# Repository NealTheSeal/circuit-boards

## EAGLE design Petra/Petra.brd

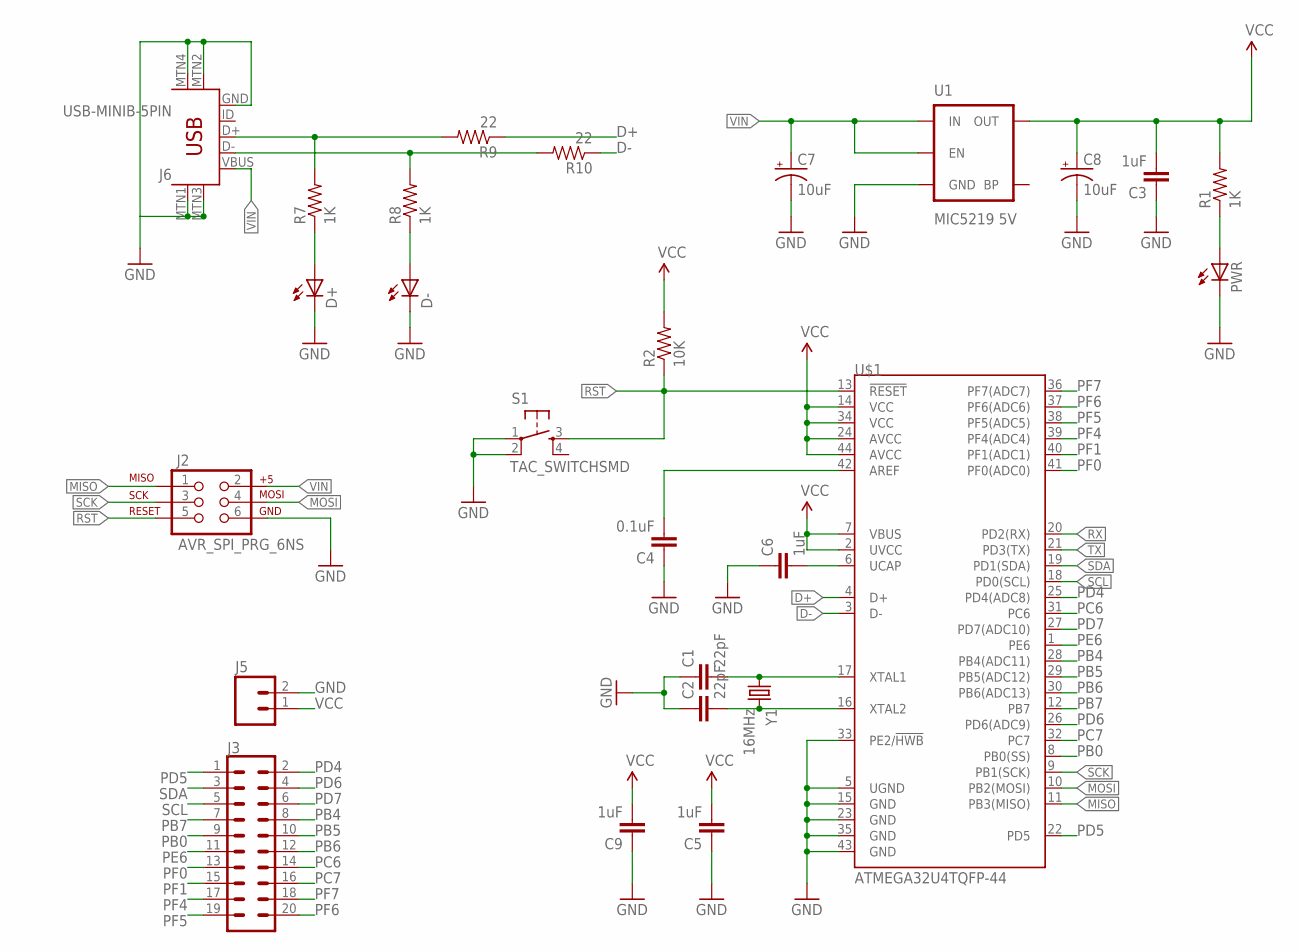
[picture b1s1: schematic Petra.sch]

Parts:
C1, C2: 22pF; 0402-CAP
C3, C5, C6, C9: 1uF; 0402-CAP
C4: 0.1uF; 0402-CAP
C7, C8: 10uF; EIA3216
D+: LEDCHIP-LED0805; CHIP-LED0805
D-: LEDCHIP-LED0805; CHIP-LED0805
J2: AVR_SPI_PRG_6NS; 2X3-NS
J3: CONN_10X2; 2X10
J5: M02PTH; 1X02
J6: USB-MINIB-5PIN; USB-MINIB
PWR: LEDCHIP-LED0805; CHIP-LED0805
R1, R7, R8: 1K; 0603-RES
R2: 10K; 0603-RES
R9, R10: 22; 0603-RES
S1: TAC_SWITCHSMD; TAC-SWITCH-PTH
U1: MIC5219 5V; SOT23-5
U$1: ATMEGA32U4TQFP-44; TQFP44
Y1: 16MHz; CRYSTAL-SMD-5X3

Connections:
D+: R9.1, U$1.4 (D+)
D-: R10.1, U$1.3 (D-)
GND: C1.1, C2.1, C3.1, C4.1, C5.1, C6.1, C7.C (-), C8.C (-), C9.1, D+.C, D-.C, J2.6, J5.2, J6.GND, J6.MTN1 (MTN2), J6.MTN2 (MTN3), J6.MTN3 (MTN1), J6.MTN4, PWR.C, S1.1, S1.2, U1.2 (GND), U$1.5 (UGND), U$1.15 (GND), U$1.23 (GND), U$1.33 (PE2/!HWB), U$1.35 (GND), U$1.43 (GND)
MISO: J2.1, U$1.11 (PB3(MISO))
MOSI: J2.4, U$1.10 (PB2(MOSI))
unnamed: C1.2, U$1.17 (XTAL1), Y1.1
unnamed: C2.2, U$1.16 (XTAL2), Y1.3 (2)
unnamed: C6.2, U$1.6 (UCAP)
unnamed: C4.2, U$1.42 (AREF)
unnamed: PWR.A, R1.1
unnamed: D-.A, R8.1
unnamed: D+.A, R7.1
unnamed: J6.D+, R7.2, R9.2
unnamed: J6.D-, R8.2, R10.2
PB0: J3.9, U$1.8 (PB0(SS))
PB4: J3.8, U$1.28 (PB4(ADC11))
PB5: J3.10, U$1.29 (PB5(ADC12))
PB6: J3.12, U$1.30 (PB6(ADC13))
PB7: J3.7, U$1.12 (PB7)
PC6: J3.14, U$1.31 (PC6)
PC7: J3.16, U$1.32 (PC7)
PD4: J3.2, U$1.25 (PD4(ADC8))
PD5: J3.1, U$1.22 (PD5)
PD6: J3.4, U$1.26 (PD6(ADC9))
PD7: J3.6, U$1.27 (PD7(ADC10))
PE6: J3.11, U$1.1 (PE6)
PF0: J3.13, U$1.41 (PF0(ADC0))
PF1: J3.15, U$1.40 (PF1(ADC1))
PF4: J3.17, U$1.39 (PF4(ADC4))
PF5: J3.19, U$1.38 (PF5(ADC5))
PF6: J3.20, U$1.37 (PF6(ADC6))
PF7: J3.18, U$1.36 (PF7(ADC7))
RST: J2.5, R2.1, S1.3, U$1.13 (!RESET)
RX: U$1.20 (PD2(RX))
SCK: J2.3, U$1.9 (PB1(SCK))
SCL: J3.5, U$1.18 (PD0(SCL))
SDA: J3.3, U$1.19 (PD1(SDA))
TX: U$1.21 (PD3(TX))
VCC: C3.2, C5.2, C8.A (+), C9.2, J5.1, R1.2, R2.2, U1.5 (OUT), U$1.2 (UVCC), U$1.7 (VBUS), U$1.14 (VCC), U$1.24 (AVCC), U$1.34 (VCC), U$1.44 (AVCC)
VIN: C7.A (+), J2.2, J6.VBUS, U1.1 (IN), U1.3 (EN)

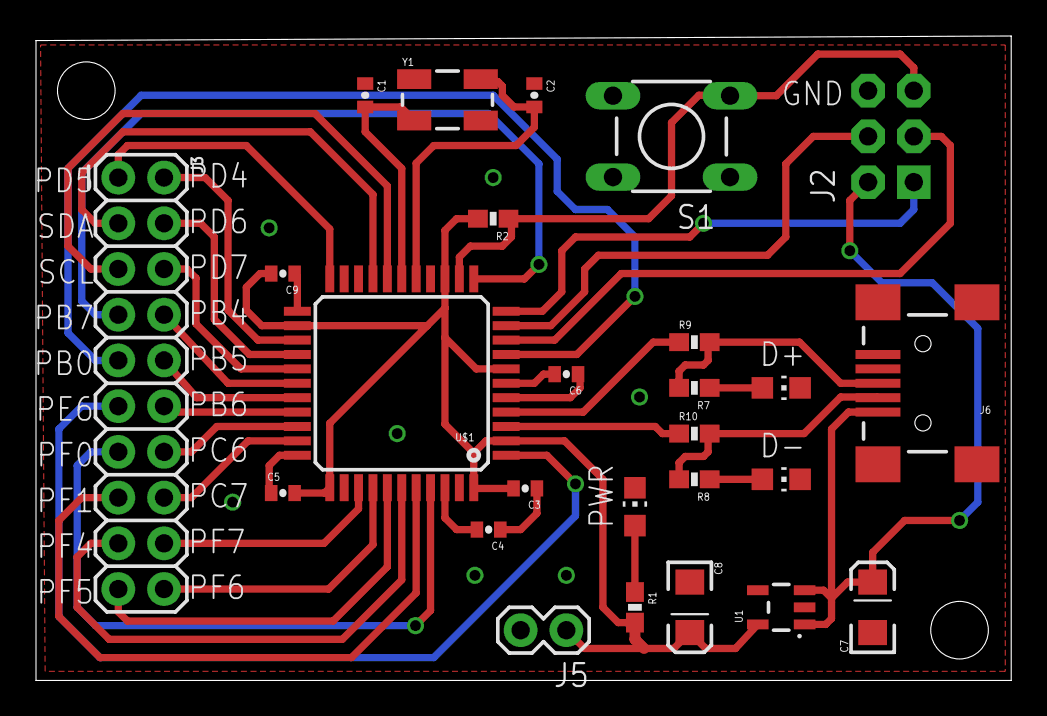
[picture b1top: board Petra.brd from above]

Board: 2 copper layers, 54.2 x 35.8 mm, 26 parts (0 on the bottom side), 38 nets.

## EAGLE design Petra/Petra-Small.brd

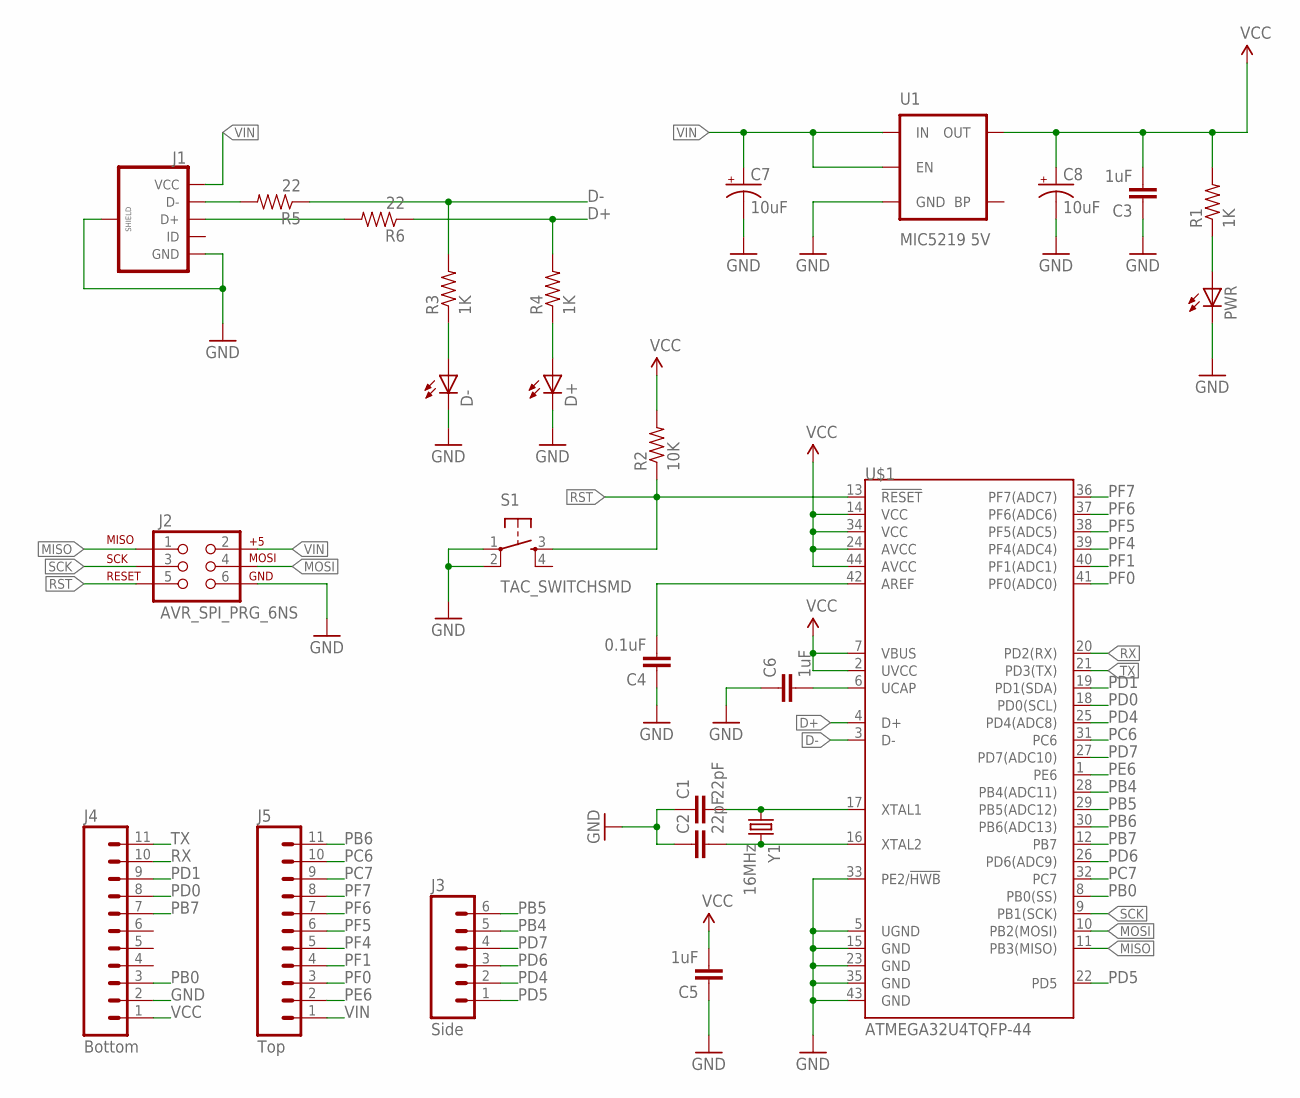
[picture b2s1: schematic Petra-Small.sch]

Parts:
C1, C2: 22pF; 0402-CAP
C3, C5, C6: 1uF; 0402-CAP
C4: 0.1uF; 0402-CAP
C7, C8: 10uF; EIA3216
D+: LEDCHIP-LED0805; CHIP-LED0805
D-: LEDCHIP-LED0805; CHIP-LED0805
J1: USB_MICROB_PLUGCONN-11752; USB-B-MICRO-SMD_V03
J2: AVR_SPI_PRG_6NS; 2X3-NS
J3: Side; 1X06
J4: Bottom; 1X11
J5: Top; 1X11
PWR: LEDCHIP-LED0805; CHIP-LED0805
R1, R3, R4: 1K; 0603-RES
R2: 10K; 0603-RES
R5, R6: 22; 0603-RES
S1: TAC_SWITCHSMD; TACTILE-SWITCH-SMD
U1: MIC5219 5V; SOT23-5
U$1: ATMEGA32U4TQFP-44; TQFP44
Y1: 16MHz; CRYSTAL-SMD-5X3

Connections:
D+: R4.2, R6.1, U$1.4 (D+)
D-: R3.2, R5.1, U$1.3 (D-)
GND: C1.1, C2.1, C3.1, C4.1, C5.1, C6.1, C7.C (-), C8.C (-), D+.C, D-.C, J1.GND, J1.SHIELD1 (SHIELD), J1.SHIELD2 (SHIELD), J1.SHIELD3 (SHIELD), J2.6, J4.2, PWR.C, S1.1, S1.2, U1.2 (GND), U$1.5 (UGND), U$1.15 (GND), U$1.23 (GND), U$1.33 (PE2/!HWB), U$1.35 (GND), U$1.43 (GND)
MISO: J2.1, U$1.11 (PB3(MISO))
MOSI: J2.4, U$1.10 (PB2(MOSI))
unnamed: C1.2, U$1.17 (XTAL1), Y1.1
unnamed: C2.2, U$1.16 (XTAL2), Y1.3 (2)
unnamed: C6.2, U$1.6 (UCAP)
unnamed: C4.2, U$1.42 (AREF)
unnamed: J1.D-, R5.2
unnamed: J1.D+, R6.2
unnamed: PWR.A, R1.1
unnamed: D+.A, R4.1
unnamed: D-.A, R3.1
PB0: J4.3, U$1.8 (PB0(SS))
PB4: J3.5, U$1.28 (PB4(ADC11))
PB5: J3.6, U$1.29 (PB5(ADC12))
PB6: J5.11, U$1.30 (PB6(ADC13))
PB7: J4.7, U$1.12 (PB7)
PC6: J5.10, U$1.31 (PC6)
PC7: J5.9, U$1.32 (PC7)
PD0: J4.8, U$1.18 (PD0(SCL))
PD1: J4.9, U$1.19 (PD1(SDA))
PD4: J3.2, U$1.25 (PD4(ADC8))
PD5: J3.1, U$1.22 (PD5)
PD6: J3.3, U$1.26 (PD6(ADC9))
PD7: J3.4, U$1.27 (PD7(ADC10))
PE6: J5.2, U$1.1 (PE6)
PF0: J5.3, U$1.41 (PF0(ADC0))
PF1: J5.4, U$1.40 (PF1(ADC1))
PF4: J5.5, U$1.39 (PF4(ADC4))
PF5: J5.6, U$1.38 (PF5(ADC5))
PF6: J5.7, U$1.37 (PF6(ADC6))
PF7: J5.8, U$1.36 (PF7(ADC7))
RST: J2.5, R2.1, S1.3, U$1.13 (!RESET)
RX: J4.10, U$1.20 (PD2(RX))
SCK: J2.3, U$1.9 (PB1(SCK))
TX: J4.11, U$1.21 (PD3(TX))
VCC: C3.2, C5.2, C8.A (+), J4.1, R1.2, R2.2, U1.5 (OUT), U$1.2 (UVCC), U$1.7 (VBUS), U$1.14 (VCC), U$1.24 (AVCC), U$1.34 (VCC), U$1.44 (AVCC)
VIN: C7.A (+), J1.VBUS (VCC), J2.2, J5.1, U1.1 (IN), U1.3 (EN)

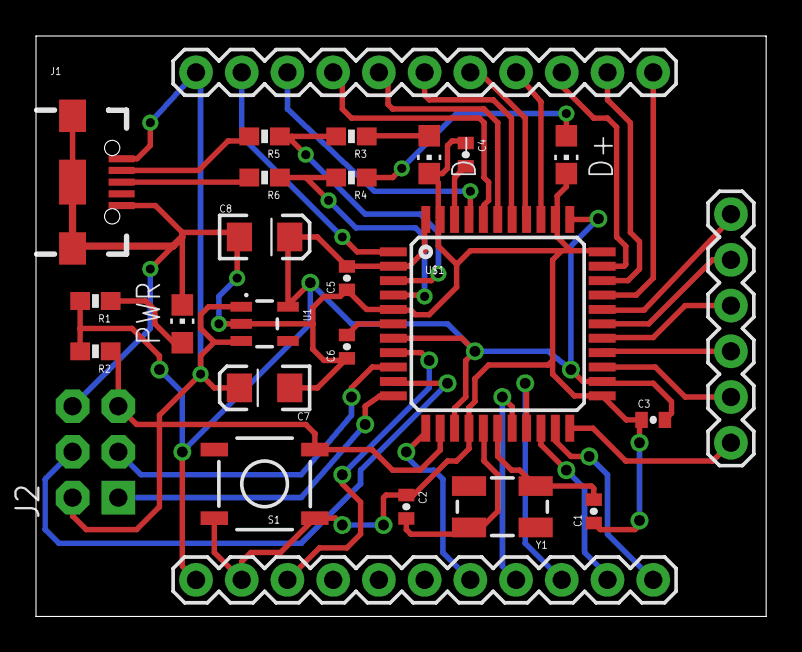
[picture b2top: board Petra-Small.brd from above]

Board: 2 copper layers, 40.6 x 32.2 mm, 26 parts (0 on the bottom side), 40 nets.

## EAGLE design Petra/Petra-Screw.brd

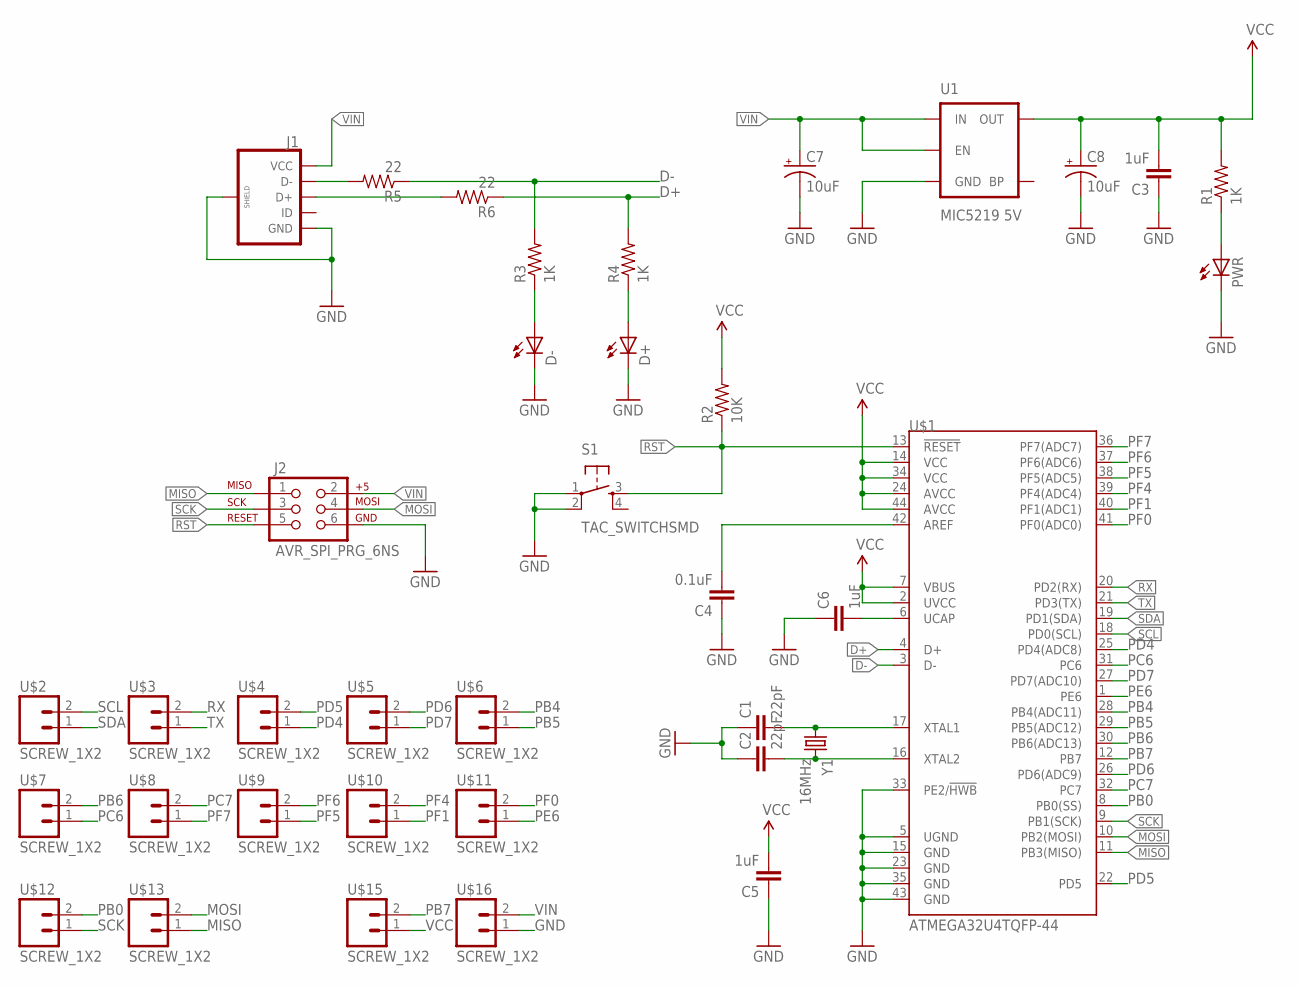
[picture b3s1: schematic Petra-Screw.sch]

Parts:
C1, C2: 22pF; 0402-CAP
C3, C5, C6: 1uF; 0402-CAP
C4: 0.1uF; 0402-CAP
C7, C8: 10uF; EIA3216
D+: LEDCHIP-LED0805; CHIP-LED0805
D-: LEDCHIP-LED0805; CHIP-LED0805
J1: USB_MICROB_PLUGCONN-11752; USB-B-MICRO-SMD_V03
J2: AVR_SPI_PRG_6NS; 2X3-NS
PWR: LEDCHIP-LED0805; CHIP-LED0805
R1, R3, R4: 1K; 0603-RES
R2: 10K; 0603-RES
R5, R6: 22; 0603-RES
S1: TAC_SWITCHSMD; TACTILE-SWITCH-SMD
U1: MIC5219 5V; SOT23-5
U$1: ATMEGA32U4TQFP-44; TQFP44
U$2, U$3, U$4, U$5, U$6, U$7, U$8, U$9, U$10, U$11, U$12, U$13, U$15, U$16: SCREW_1X2; 1X2-SCREW
Y1: 16MHz; CRYSTAL-SMD-5X3

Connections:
D+: R4.2, R6.1, U$1.4 (D+)
D-: R3.2, R5.1, U$1.3 (D-)
GND: C1.1, C2.1, C3.1, C4.1, C5.1, C6.1, C7.C (-), C8.C (-), D+.C, D-.C, J1.GND, J1.SHIELD1 (SHIELD), J1.SHIELD2 (SHIELD), J1.SHIELD3 (SHIELD), J2.6, PWR.C, S1.1, S1.2, U1.2 (GND), U$1.5 (UGND), U$1.15 (GND), U$1.23 (GND), U$1.33 (PE2/!HWB), U$1.35 (GND), U$1.43 (GND), U$16.1
MISO: J2.1, U$1.11 (PB3(MISO)), U$13.1
MOSI: J2.4, U$1.10 (PB2(MOSI)), U$13.2
unnamed: C1.2, U$1.17 (XTAL1), Y1.1
unnamed: C2.2, U$1.16 (XTAL2), Y1.3 (2)
unnamed: C6.2, U$1.6 (UCAP)
unnamed: C4.2, U$1.42 (AREF)
unnamed: J1.D-, R5.2
unnamed: J1.D+, R6.2
unnamed: PWR.A, R1.1
unnamed: D+.A, R4.1
unnamed: D-.A, R3.1
PB0: U$1.8 (PB0(SS)), U$12.2
PB4: U$1.28 (PB4(ADC11)), U$6.2
PB5: U$1.29 (PB5(ADC12)), U$6.1
PB6: U$1.30 (PB6(ADC13)), U$7.2
PB7: U$1.12 (PB7), U$15.2
PC6: U$1.31 (PC6), U$7.1
PC7: U$1.32 (PC7), U$8.2
PD4: U$1.25 (PD4(ADC8)), U$4.1
PD5: U$1.22 (PD5), U$4.2
PD6: U$1.26 (PD6(ADC9)), U$5.2
PD7: U$1.27 (PD7(ADC10)), U$5.1
PE6: U$1.1 (PE6), U$11.1
PF0: U$1.41 (PF0(ADC0)), U$11.2
PF1: U$1.40 (PF1(ADC1)), U$10.1
PF4: U$1.39 (PF4(ADC4)), U$10.2
PF5: U$1.38 (PF5(ADC5)), U$9.1
PF6: U$1.37 (PF6(ADC6)), U$9.2
PF7: U$1.36 (PF7(ADC7)), U$8.1
RST: J2.5, R2.1, S1.3, U$1.13 (!RESET)
RX: U$1.20 (PD2(RX)), U$3.2
SCK: J2.3, U$1.9 (PB1(SCK)), U$12.1
SCL: U$1.18 (PD0(SCL)), U$2.2
SDA: U$1.19 (PD1(SDA)), U$2.1
TX: U$1.21 (PD3(TX)), U$3.1
VCC: C3.2, C5.2, C8.A (+), R1.2, R2.2, U1.5 (OUT), U$1.2 (UVCC), U$1.7 (VBUS), U$1.14 (VCC), U$1.24 (AVCC), U$1.34 (VCC), U$1.44 (AVCC), U$15.1
VIN: C7.A (+), J1.VBUS (VCC), J2.2, U1.1 (IN), U1.3 (EN), U$16.2

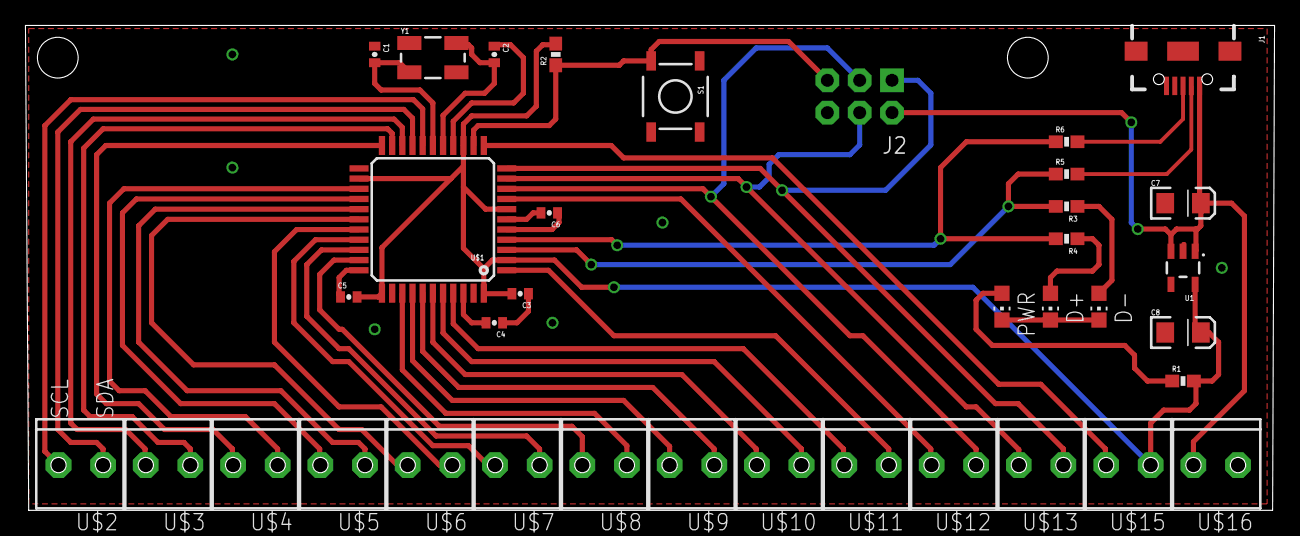
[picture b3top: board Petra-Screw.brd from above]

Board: 2 copper layers, 98.1 x 38.1 mm, 37 parts (0 on the bottom side), 40 nets.

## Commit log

2016-11-20 adding first rev of Petra
2016-12-28 adding ignore file
2016-12-28 Adding old revisions and library file.
2016-12-29 Created Screw Terminal Board. Cleaned up folder structure.
2017-01-02 Made screw terminal board smaller. Added BOM for Petra
2017-01-30 moving to 20 pin io connector
2017-01-30 Completed io change. Reduced board size
2017-02-01 Changed usb and button part. Reduced board size even further.

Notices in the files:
parts and their libraries:
SparkFun-Passives: Licensing: Creative Commons ShareAlike 4.0 International - https://creativecommons.org/licenses/by-sa/4.0
